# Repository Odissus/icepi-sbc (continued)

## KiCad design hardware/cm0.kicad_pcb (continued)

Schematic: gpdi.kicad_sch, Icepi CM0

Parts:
C108: 100nF; C_0402_1005Metric; LCSC Part # C1525
D1, D2: 1N5819WS; D_SOD-323; LCSC Part # C191023
J5: GPDI_A; GPDI_A_XUNPU_001S; LCSC Part # C720616
Q3: BSN20; SOT-23; LCSC Part # C116157
R37, R38: 33k; R_0402_1005Metric; LCSC Part # C25779
R39, R40: 2k; R_0402_1005Metric; LCSC Part # C4109
U19, U20, U23: UCL0524P; Diodes_UDFN-10_1.0x2.5mm_P0.5mm; LCSC Part # C2835428

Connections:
+3V3: D1.2 (A), Q3.1 (G), R37.1; also elsewhere on the board
+5V: D2.2 (A), R39.2, R40.2; also elsewhere on the board
/GPDI/GPDI_CEC: Q3.2 (S), R37.2; also elsewhere on the board
/GPDI/GPDI_CECI: J5.13 (CEC), Q3.3 (D), R38.2, U23.1, U23.10
/GPDI/GPDI_CLK+: J5.10 (CK+), U20.4, U20.7; also elsewhere on the board
/GPDI/GPDI_CLK-: J5.12 (CK-), U20.5, U20.6; also elsewhere on the board
/GPDI/GPDI_D0+: J5.7 (D0+), U20.1, U20.10; also elsewhere on the board
/GPDI/GPDI_D0-: J5.9 (D0-), U20.2, U20.9; also elsewhere on the board
/GPDI/GPDI_D1+: J5.4 (D1+), U19.4, U19.7; also elsewhere on the board
/GPDI/GPDI_D1-: J5.6 (D1-), U19.5, U19.6; also elsewhere on the board
/GPDI/GPDI_D2+: J5.1 (D2+), U19.1, U19.10; also elsewhere on the board
/GPDI/GPDI_D2-: J5.3 (D2-), U19.2, U19.9; also elsewhere on the board
/GPDI/GPDI_HPD: J5.19 (HPD), U23.5, U23.6; also elsewhere on the board
/GPDI/GPDI_SCL: J5.15 (SCL), R40.1, U23.2, U23.9; also elsewhere on the board
/GPDI/GPDI_SDA: J5.16 (SDA), R39.1, U23.4, U23.7; also elsewhere on the board
GND: C108.1, J5.2 (D2S), J5.5 (D1S), J5.8 (D0S), J5.11 (CKS), J5.17 (GND), J5.SH, U19.3, U19.8, U20.3, U20.8, U23.3, U23.8; also elsewhere on the board
unnamed: D1.1 (K), R38.1
unnamed: C108.2, D2.1 (K), J5.18 (+5V)

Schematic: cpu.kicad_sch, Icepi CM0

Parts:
C1, C2, C3, C4, C7, C8, C9, C12, C14, C18, C19, C23, C24, C26, C27, C29, C31, C37, C38, C130: 100nF; C_0402_1005Metric; LCSC Part # C1525
C10, C11, C32, C129: 4.7uF; C_0402_1005Metric; LCSC Part # C23733
C13, C16, C17, C21, C22, C25, C33, C35, C36: 1uF; C_0402_1005Metric; LCSC Part # C52923
C15, C20, C28, C30: 10uF; C_0603_1608Metric; LCSC Part # C19702
C34, C39, C127, C128: 15pF; C_0402_1005Metric; LCSC Part # C1548
Q5: MMBT3904; SOT-23; LCSC Part # C20526
R1: 6.04k; R_0402_1005Metric; LCSC Part # C25913
R2: 240; R_0603_1608Metric; LCSC Part # C23350
R3, R5: 0; R_0402_1005Metric; LCSC Part # C17168
R4: 220k; R_0402_1005Metric; LCSC Part # C25767
R6: 10M; R_0402_1005Metric; LCSC Part # C26082
R61, R66, R67, R68: 47k; R_0402_1005Metric; LCSC Part # C25792
R62: 100k; R_0402_1005Metric; LCSC Part # C25741
R63, R64, R65: 10k; R_0402_1005Metric; LCSC Part # C25744
TP1, TP2, TP3: TestPoint; TestPoint_Pad_D1.0mm; not fitted
U1: H3; FBGA-347_14x14mm_Layout21x21_P0.65mm; LCSC Part # C94644
Y1: 32kHz; Crystal_SMD_3215-2Pin_3.2x1.5mm; LCSC Part # C32346
Y3: 24MHz; Crystal_SMD_2016-4Pin_2.0x1.6mm; LCSC Part # C362340

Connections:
+1V1_CPUX: C15.1, C16.2, C17.2, C18.2, C19.2, U1.N8 (VDD-CPUX), U1.P6 (VDD-CPUX), U1.P7 (VDD-CPUX), U1.P8 (VDD-CPUX), U1.P9 (VDD-CPUX), U1.R6 (VDD-CPUX), U1.R7 (VDD-CPUX), U1.R8 (VDD-CPUX), U1.T6 (VDD-CPUX), U1.T7 (VDD-CPUX), U1.T8 (VDD-CPUX), U1.U6 (VDD-CPUX), U1.U9 (VDD-CPUX); also elsewhere on the board
+1V2_SYSTEM: C4.2, C20.1, C21.2, C22.2, C23.2, C24.2, U1.F8 (EPHY_VDD), U1.H10 (VDD-SYS), U1.J10 (VDD-SYS), U1.J11 (VDD-SYS), U1.J12 (VDD-SYS), U1.K10 (VDD-SYS), U1.K11 (VDD-SYS), U1.K12 (VDD-SYS), U1.L10 (VDD-SYS), U1.L11 (VDD-SYS), U1.L12 (VDD-SYS), U1.L13 (VDD-SYS), U1.L14 (VDD-SYS); also elsewhere on the board
+1V5: C35.2, C36.2, C37.2, C38.2, U1.L16 (VCC-DRAM), U1.M16 (VCC-DRAM), U1.N16 (VCC-DRAM), U1.P16 (VCC-DRAM), U1.P17 (VCC-DRAM), U1.R16 (VCC-DRAM), U1.T12 (VCC-DRAM), U1.T13 (VCC-DRAM), U1.T14 (VCC-DRAM), U1.T15 (VCC-DRAM), U1.U11 (VCC-DRAM); also elsewhere on the board
+3V3_AVCC: C7.2, C12.2, C27.2, C28.1, C29.2, R61.1, R62.1, R65.1, R66.1, R68.1, U1.G9 (V33_TV), U1.K6 (VCC_RTC), U1.N3 (VCC_PLL), U1.V3 (AVCC); also elsewhere on the board
+3V3_IO: C1.2, C2.2, C3.2, C8.2, C13.2, C14.2, C129.1, R67.1, U1.G7 (EPHY_VCC), U1.G11 (VCC_USB), U1.G13 (VCC-IO), U1.G14 (VCC-IO), U1.G15 (VCC-IO), U1.H7 (VCC-PG), U1.H11 (VDD-EFUSEEBP), U1.H13 (VCC-IO), U1.H14 (VCC-IO), U1.J6 (GPDI_VCC), U1.J14 (VCC-IO), U1.J15 (VCC_PD); also elsewhere on the board
/Audio/AUDIO_L: U1.AA3 (LINEOUTL); also elsewhere on the board
/Audio/AUDIO_R: U1.Y3 (LINEOUTR); also elsewhere on the board
/Audio/TV_OUT: U1.F10 (TVOUT); also elsewhere on the board
/DDR3/A0: U1.T17 (SA0); also elsewhere on the board
/DDR3/A1: U1.U18 (SA1); also elsewhere on the board
/DDR3/A2: U1.V19 (SA2); also elsewhere on the board
/DDR3/A3: U1.V20 (SA3); also elsewhere on the board
/DDR3/A4: U1.V21 (SA4); also elsewhere on the board
/DDR3/A5: U1.Y19 (SA5); also elsewhere on the board
/DDR3/A6: U1.Y20 (SA6); also elsewhere on the board
/DDR3/A7: U1.V15 (SA7); also elsewhere on the board
/DDR3/A8: U1.W18 (SA8); also elsewhere on the board
/DDR3/A9: U1.Y18 (SA9); also elsewhere on the board
/DDR3/A10: U1.P19 (SA10); also elsewhere on the board
/DDR3/A11: U1.N19 (SA11); also elsewhere on the board
/DDR3/A12: U1.R18 (SA12); also elsewhere on the board
/DDR3/A13: U1.V12 (SA13); also elsewhere on the board
/DDR3/A14: U1.N17 (SA14); also elsewhere on the board
/DDR3/A15: U1.R17 (SA15); also elsewhere on the board
/DDR3/BA0: U1.W17 (SBA0); also elsewhere on the board
/DDR3/BA1: U1.T18 (SBA1); also elsewhere on the board
/DDR3/BA2: U1.V17 (SBA2); also elsewhere on the board
/DDR3/CKE: U1.AA21 (SCKE0); also elsewhere on the board
/DDR3/CLK+: U1.AA19 (SCK); also elsewhere on the board
/DDR3/CLK-: U1.AA20 (SCKB); also elsewhere on the board
/DDR3/DQ0: U1.T20 (SDQ5); also elsewhere on the board
/DDR3/DQ1: U1.P20 (SDQ2); also elsewhere on the board
/DDR3/DQ2: U1.U19 (SDQ6); also elsewhere on the board
/DDR3/DQ3: U1.N20 (SDQ0); also elsewhere on the board
/DDR3/DQ4: U1.U20 (SDQ7); also elsewhere on the board
/DDR3/DQ5: U1.P21 (SDQ1); also elsewhere on the board
/DDR3/DQ6: U1.U21 (SDQ3); also elsewhere on the board
/DDR3/DQ7: U1.R19 (SDQ4); also elsewhere on the board
/DDR3/DQ8: U1.J21 (SDQ11); also elsewhere on the board
/DDR3/DQ9: U1.M21 (SDQ14); also elsewhere on the board
/DDR3/DQ10: U1.H21 (SDQ10); also elsewhere on the board
/DDR3/DQ11: U1.M19 (SDQ15); also elsewhere on the board
/DDR3/DQ12: U1.J19 (SDQ8); also elsewhere on the board
/DDR3/DQ13: U1.L21 (SDQ13); also elsewhere on the board
/DDR3/DQ14: U1.H20 (SDQ9); also elsewhere on the board
/DDR3/DQ15: U1.L20 (SDQ12); also elsewhere on the board
/DDR3/DQ16: U1.Y17 (SDQ16)
/DDR3/DQ17: U1.AA17 (SDQ17)
/DDR3/DQ18: U1.Y16 (SDQ18)
/DDR3/DQ19: U1.W15 (SDQ19)
/DDR3/DQ20: U1.Y14 (SDQ20)
/DDR3/DQ21: U1.AA14 (SDQ21)
/DDR3/DQ22: U1.Y13 (SDQ22)
/DDR3/DQ23: U1.Y12 (SDQ23)
/DDR3/DQ24: U1.W12 (SDQ24)
/DDR3/DQ25: U1.AA11 (SDQ25)
/DDR3/DQ26: U1.Y11 (SDQ26)
/DDR3/DQ27: U1.Y10 (SDQ27)
/DDR3/DQ28: U1.W9 (SDQ28)
/DDR3/DQ29: U1.AA8 (SDQ29)
/DDR3/DQ30: U1.Y8 (SDQ30)
/DDR3/DQ31: U1.Y7 (SDQ31)
/DDR3/DQM0: U1.M20 (SDQM0); also elsewhere on the board
/DDR3/DQM1: U1.G20 (SDQM1); also elsewhere on the board
/DDR3/DQM2: U1.AA18 (SDQM2)
/DDR3/DQM3: U1.AA12 (SDQM3)
/DDR3/DQS0+: U1.R20 (SDQS0); also elsewhere on the board
/DDR3/DQS0-: U1.R21 (SDQS0B); also elsewhere on the board
/DDR3/DQS1+: U1.K20 (SDQS1); also elsewhere on the board
/DDR3/DQS1-: U1.J20 (SDQS1B); also elsewhere on the board
/DDR3/DQS2+: U1.AA15 (SDQS2)
/DDR3/DQS2-: U1.Y15 (SDQS2B)
/DDR3/DQS3+: U1.AA9 (SDQS3)
/DDR3/DQS3-: U1.Y9 (SDQS3B)
/DDR3/ODT: U1.W11 (SODT0); also elsewhere on the board
/DDR3/~CAS: U1.U15 (SCAS); also elsewhere on the board
/DDR3/~CS: U1.W20 (SCS0); also elsewhere on the board
/DDR3/~RAS: U1.V13 (SRAS); also elsewhere on the board
/DDR3/~RESET: U1.U16 (SRST); also elsewhere on the board
/DDR3/~WE: U1.W13 (SWE); also elsewhere on the board
/GPDI/GPDI_CEC: U1.G5 (GPDI_CEC); also elsewhere on the board
/GPDI/GPDI_CLK+: U1.F2 (GPDI_CLK+); also elsewhere on the board
/GPDI/GPDI_CLK-: U1.E2 (GPDI_CLK-); also elsewhere on the board
/GPDI/GPDI_D0+: U1.G1 (GPDI_D0+); also elsewhere on the board
/GPDI/GPDI_D0-: U1.F1 (GPDI_D0-); also elsewhere on the board
/GPDI/GPDI_D1+: U1.H2 (GPDI_D1+); also elsewhere on the board
/GPDI/GPDI_D1-: U1.G2 (GPDI_D1-); also elsewhere on the board
/GPDI/GPDI_D2+: U1.J1 (GPDI_D2+); also elsewhere on the board
/GPDI/GPDI_D2-: U1.J2 (GPDI_D2-); also elsewhere on the board
/GPDI/GPDI_HPD: U1.M2 (GPDI_HPD); also elsewhere on the board
/GPDI/GPDI_SCL: U1.H3 (GPDI_SCL); also elsewhere on the board
/GPDI/GPDI_SDA: U1.K3 (GPDI_SDA); also elsewhere on the board
/GPIO/CPU_RX: U1.H6 (PA5); also elsewhere on the board
/GPIO/CPU_TX: U1.F5 (PA4); also elsewhere on the board
/H3/AGND: C28.2, C29.1, C30.2, C31.1, C32.2, C33.1, R4.2, R5.1, U1.U3 (AGND)
/H3/BT_HOST_WAKE: U1.P2 (PL2); also elsewhere on the board
/H3/BT_RXD: U1.D3 (UART1_RX); also elsewhere on the board
/H3/BT_TXD: U1.G4 (UART1_TX); also elsewhere on the board
/H3/BT_WAKE: U1.A13 (PA20); also elsewhere on the board
/H3/EPHY_LINK_LED: U1.A2 (EPHY_LINK_LED); also elsewhere on the board
/H3/EPHY_RX+: U1.B4 (EPHY_RXP); also elsewhere on the board
/H3/EPHY_RX-: U1.A4 (EPHY_RXN); also elsewhere on the board
/H3/EPHY_SPD_LED: U1.F7 (EPHY_SPD_LED); also elsewhere on the board
/H3/EPHY_TX+: U1.B3 (EPHY_TXP); also elsewhere on the board
/H3/EPHY_TX-: U1.A3 (EPHY_TXN); also elsewhere on the board
/H3/KEYADC: R62.2, U1.AA5 (KEYADC)
/H3/PWR_CPUFB: TP1.1, U1.T10 (VDD-CPUFB); also elsewhere on the board
/H3/PWR_DRAM: U1.M6 (PL9); also elsewhere on the board
/H3/PWR_IO: U1.R2 (PL5); also elsewhere on the board
/H3/PWR_KEY: R66.2, U1.R1 (PL3)
/H3/PWR_SYSTEM: U1.T2 (PL8); also elsewhere on the board
/H3/PWR_VSET: U1.T4 (PL6); also elsewhere on the board
/H3/RECOVERY: R68.2, U1.N2 (PL4)
/H3/RESET: C130.2, Q5.3 (C), R65.2, U1.V6 (RESET)
/H3/SDIO_CLK: U1.J3 (SDC1_CLK); also elsewhere on the board
/H3/SDIO_CMD: U1.L2 (SDC1_CMD); also elsewhere on the board
/H3/SDIO_D0: U1.H4 (SDC1_D0); also elsewhere on the board
/H3/SDIO_D1: U1.F3 (SDC1_D1); also elsewhere on the board
/H3/SDIO_D2: U1.C2 (SDC1_D2); also elsewhere on the board
/H3/SDIO_D3: U1.C1 (SDC1_D3); also elsewhere on the board
/H3/SD_CLK: U1.D20 (PF2); also elsewhere on the board
/H3/SD_CMD: U1.F18 (PF3); also elsewhere on the board
/H3/SD_D0: U1.A19 (PF1); also elsewhere on the board
/H3/SD_D1: U1.D19 (PF0); also elsewhere on the board
/H3/SD_D2: U1.C20 (PF5); also elsewhere on the board
/H3/SD_D3: U1.E21 (PF4); also elsewhere on the board
/H3/SD_DET: U1.G18 (PF6); also elsewhere on the board
/H3/UBOOT: R67.2, U1.W6 (UBOOT)
/H3/USB_D0+: U1.A5 (USB_D0+); also elsewhere on the board
/H3/USB_D0-: U1.B5 (USB_D0-); also elsewhere on the board
/H3/USB_D1+: U1.B6 (USB_D1+); also elsewhere on the board
/H3/USB_D1-: U1.B7 (USB_D1-); also elsewhere on the board
/H3/VRA1: C33.2, U1.Y4 (VRA1)
/H3/VRA2: C32.1, R4.1, U1.W5 (VRA2)
/H3/VRP: C30.1, C31.2, U1.V4 (VRP)
/H3/WIFI_32K: U1.P3 (X32KFOUT); also elsewhere on the board
/H3/WL_HOST_WAKE: U1.T3 (PL7); also elsewhere on the board
/H3/WL_REG_ON: U1.F13 (PA8); also elsewhere on the board
/H3/X24MI: C127.1, U1.K2 (X24MIN), Y3.2
/H3/X24MO: C128.1, U1.K1 (X24MOUT), Y3.4
/H3/X32KI: C34.1, R6.1, U1.V5 (X32KIN), Y1.2
/H3/X32KO: C39.1, R6.2, U1.U4 (X32KOUT), Y1.1
/H3/eMMC_CLK: U1.A17 (PC5); also elsewhere on the board
/H3/eMMC_CMD: U1.E16 (PC6); also elsewhere on the board
/H3/eMMC_D0: U1.B18 (PC8); also elsewhere on the board
/H3/eMMC_D1: U1.C17 (PC9); also elsewhere on the board
/H3/eMMC_D2: U1.D17 (PC10); also elsewhere on the board
/H3/eMMC_D3: U1.C18 (PC11); also elsewhere on the board
/H3/eMMC_D4: U1.B17 (PC12); also elsewhere on the board
/H3/eMMC_D5: U1.B19 (PC13); also elsewhere on the board
/H3/eMMC_D6: U1.F17 (PC14); also elsewhere on the board
/H3/eMMC_D7: U1.C19 (PC15); also elsewhere on the board
/H3/~BT_CTS: U1.E3 (UART1_CTS); also elsewhere on the board
/H3/~BT_RST: U1.D13 (PA9); also elsewhere on the board
/H3/~BT_RTS: U1.C3 (UART1_RTS); also elsewhere on the board
/H3/~eMMC_RST: U1.H16 (PC16); also elsewhere on the board
GND: C1.1, C2.1, C3.1, C4.1, C7.1, C8.1, C9.2, C10.2, C11.2, C12.1, C13.1, C14.1, C15.2, C16.1, C17.1, C18.1, C19.1, C20.2, C21.1, C22.1, C23.1, C24.1, C25.1, C26.1, C27.1, C34.2, C35.1, C36.1, C37.1, C38.1, C39.2, C127.2, C128.2, C130.1, Q5.2 (E), R1.2, R2.1, R3.2, R5.2, R63.2, U1.A21 (GND), U1.AA1 (GND), U1.G8 (GND), U1.H8 (GND_TV), U1.H12 (GND), U1.H15 (GND), U1.J9 (GND), U1.J13 (GND), U1.J16 (GND), U1.K7 (GND), U1.K8 (GND), U1.K9 (GND), U1.K13 (GND), U1.K14 (GND), U1.K15 (GND), U1.K16 (GND), U1.L8 (GND), U1.L9 (GND), U1.L15 (GND), U1.M5 (GPDI_GND), U1.M7 (GND), U1.M8 (GND), U1.M9 (GND), U1.M10 (GND), U1.M11 (GND), U1.M12 (GND), U1.M13 (GND), U1.M14 (GND), U1.M15 (GND), U1.N7 (GND), U1.N9 (GND), U1.N10 (GND), U1.N11 (GND), U1.N12 (GND), U1.N13 (GND), U1.N14 (GND), U1.N15 (GND), U1.P10 (GND), U1.P11 (GND), U1.P12 (GND), U1.P13 (GND), U1.P14 (GND), U1.P15 (GND), U1.R9 (GND), U1.R10 (GND), U1.R11 (GND), U1.R12 (GND), U1.R13 (GND), U1.R14 (GND), U1.T11 (GND), Y3.1, Y3.3; also elsewhere on the board
unnamed: C129.2, R63.1, R64.1
unnamed: Q5.1 (B), R64.2
unnamed: R2.2, U1.V10 (SZQ)
unnamed: C10.1, U1.G10 (VDD-EFUSE)
unnamed: R1.1, U1.F6 (EPHY_RTX)
unnamed: R3.1, U1.T9 (GND-CPUFB)
unnamed: TP2.1, U1.A1 (JTAG-SEL0)
unnamed: TP3.1, U1.B2 (JTAG-SEL1)
unnamed: R61.2, U1.AA6 (NMI)
VDD_CPUS: C11.1, C25.2, C26.2, U1.J7 (VDD-CPUS), U1.J8 (VDD-CPUS), U1.M4 (RTC_VIO)
VREF: C9.1, U1.T16 (SVREF); also elsewhere on the board

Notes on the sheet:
Accessible via resistor
USB0 is OTG
This isn't a laptop so no power key & KEYADC
FIXME: KEYADC

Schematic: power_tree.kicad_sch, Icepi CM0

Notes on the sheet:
1.2V/2A
3.3V/1A
1.5V/1A
1.3V/3A
H3 Debugging Guide
3.3V/0.5A
DRAM
SY8089A
SY8088
VCC-IO 3.3v AVCC 3.3v VCC-RTC 3.3v VCC3V-PLL 3.3v VCC3V-TV 3.3v VCC-DRAM 1.5v VDD-CPUX 1.3v VDD1V1-EPHY 1.2v VDD1V2-SYS 1.2v
AVCC
USB-C PD 5V/5A (25W)
SY8113
VCC-CPUX
VCC-IO
RTC
SY8088 1A 1.5MHz SY8089A 2A 1MHz SY8113B 3A 0.5MHz
SYSTEM
VCC-WIFI

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
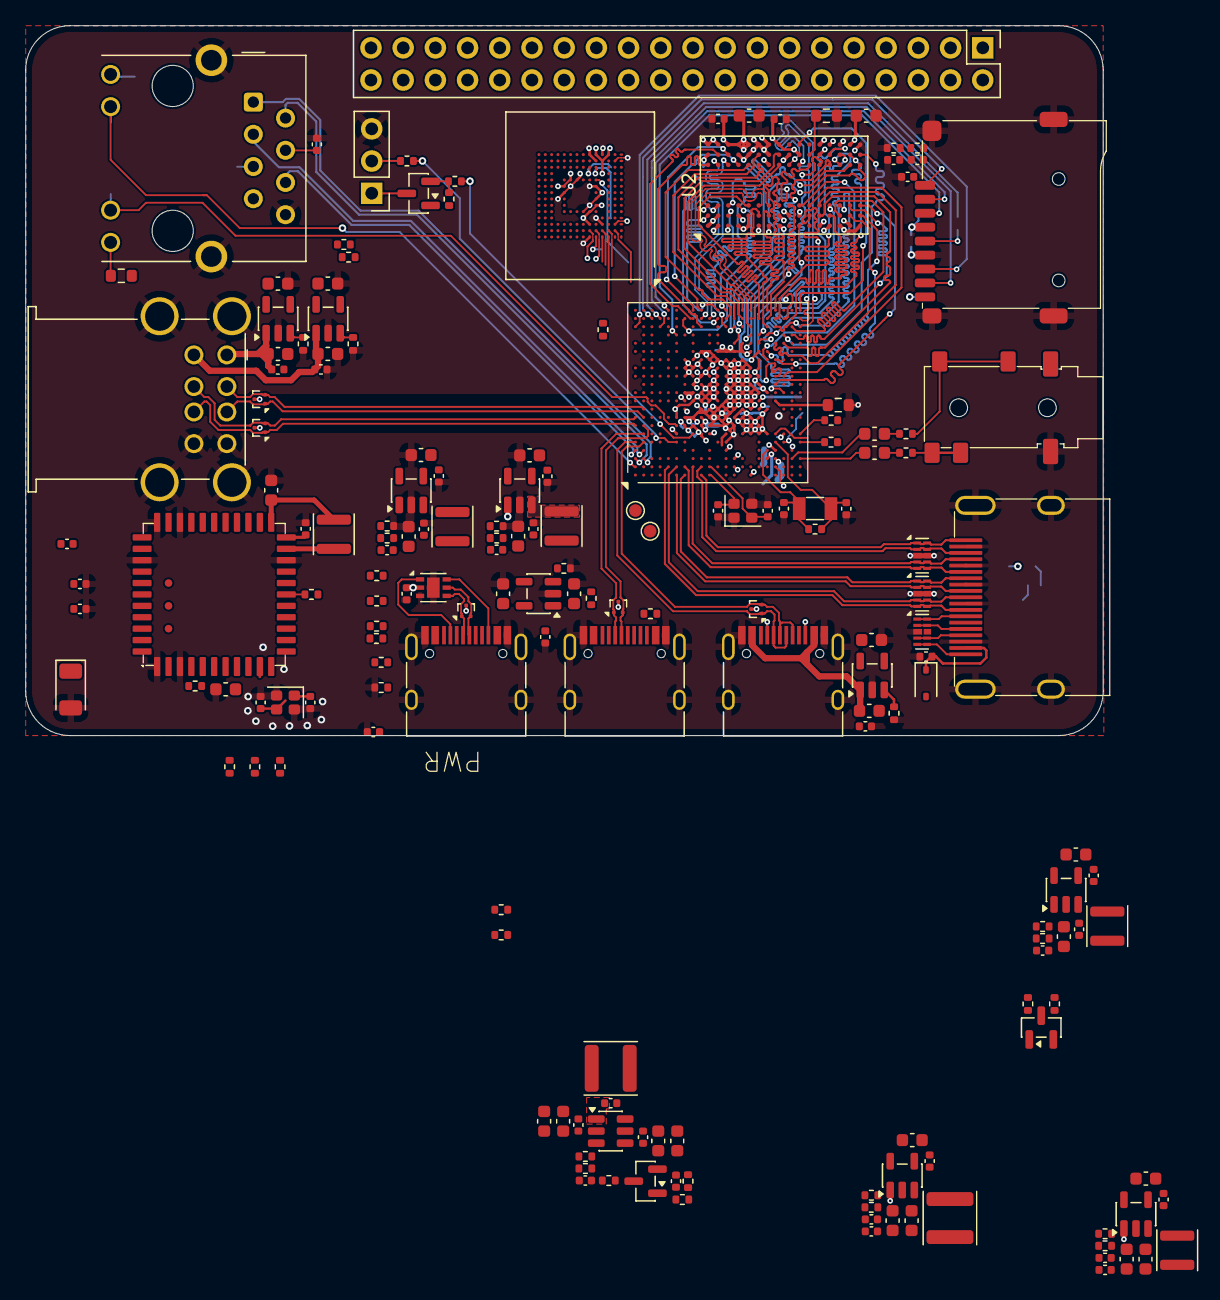
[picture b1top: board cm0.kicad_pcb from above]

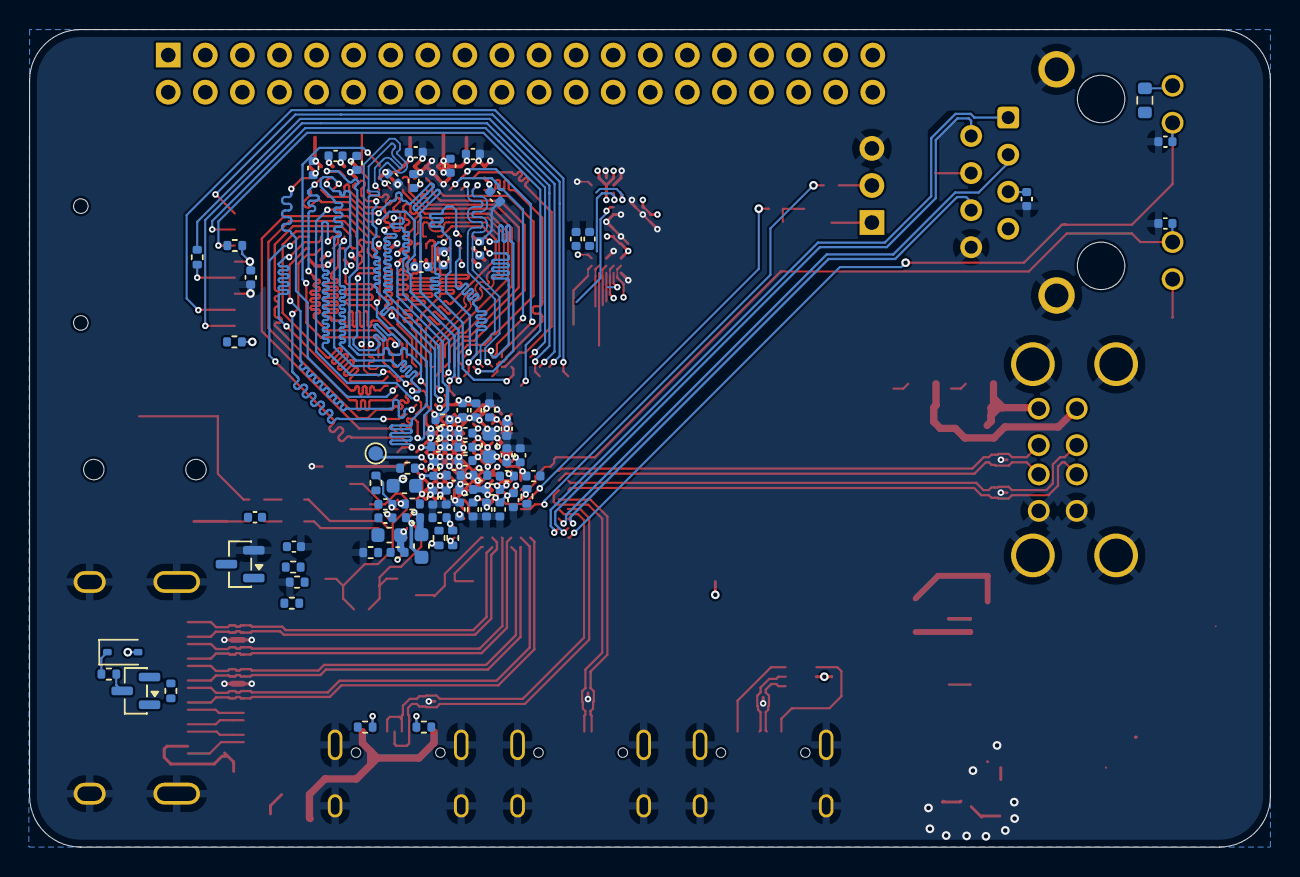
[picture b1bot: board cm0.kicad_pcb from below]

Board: 4 copper layers, 85.0 x 56.0 mm, 252 parts (77 on the bottom side), 209 nets.

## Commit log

2025-11-04 Decoupled DDR3 and drew RJ45 connector
2025-11-08 Initial layout
2025-11-10 Finished DC DC converters and started decoupling the CPU
2025-11-11 Decoupling on PCB side almost done
2025-11-12 Routed DCDC, EPHY and SD
2025-11-15 Fix typo
2025-11-15 Add Solderpad license
2025-12-06 Docs
2025-12-19 Update crystal
2025-12-20 Changed crystal and fix USB data lines
2025-12-22 Updated README and improved audio routing
2025-12-22 Add schematic pdf
2025-12-24 DDR3 benchmark
